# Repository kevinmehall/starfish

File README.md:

This tiny board provides a 12-pin Pmod port, controlled over USB. [Pmod](http://www.digilentinc.com/Pmods/Digilent-Pmod_%20Interface_Specification.pdf) is a standard pinout for SPI, I2C, UART, and GPIO on a 6 or 12 pin connector, with over 100 modules available from several companies. 

Level shifters and a digitally-controlled voltage regulator allow it to operate at 1.2 - 5V IO levels. 

Key components:

  * [Atmel SAMD21](http://www.atmel.com/Images/Atmel-42181-SAM-D21_Datasheet.pdf) - Cortex M0+ microcontroller
  * [Fairchild FXMAR2104](https://www.fairchildsemi.com/datasheets/FX/FXMAR2104.pdf) - IO level shifter

Firmware bringup is in progress. It will work with the [Tessel 2 JavaScript API](https://github.com/tessel/t2-firmware) and [Signalspec](http://signalspec.org).

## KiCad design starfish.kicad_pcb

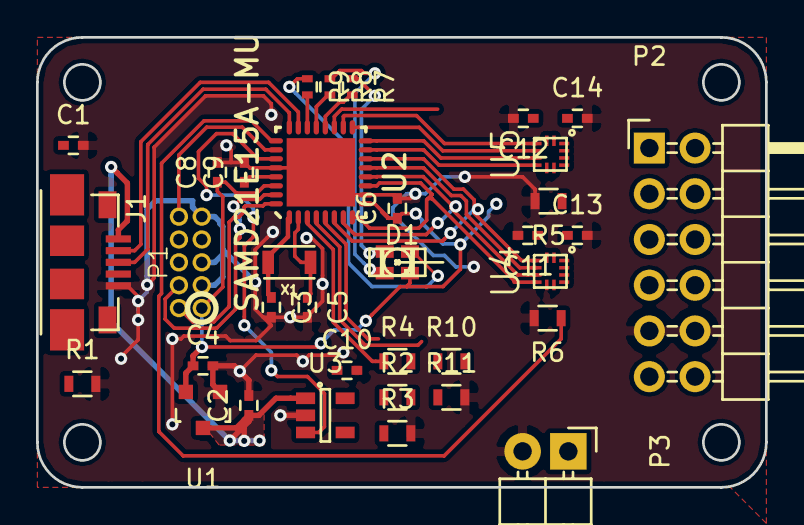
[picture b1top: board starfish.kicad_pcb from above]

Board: 2 copper layers, 40.5 x 25.0 mm, 35 parts (0 on the bottom side), 42 nets.

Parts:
C1, C3, C5: 10pF; C_0402
C2, C4, C10: 1uF; C_0402
C6, C8, C9, C11, C12, C13, C14: 100nF; C_0402
D1: LED-RGB-COMMON-ANODE; LED-1206-RGB
J1: microUSB; MICRO-USB-10104111
P1: CONN_02X05; CONN_02x05_0.05in
P2: CONN_6X2; Pin_Header_Angled_2x06
P3: CONN_2; Pin_Header_Angled_1x02
R1, R2, R3, R4, R5, R6, R10, R11: R; R_0603
R7, R8, R9: 120; R_0402
U1: AP2120N; SOT-23
U2: SAMD21E15A-MU; QFP32
U3: TPS73101; SOT-23-5
U4, U5: FXMAR2104; UMLP-12
X1: CRYSTAL; FC-135

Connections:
+3.3V: C4.1, C6.1, C8.1, C11.1, C12.1, D1.4, P1.1, U1.2, U2.9, U2.30, U4.2, U5.2
+5V: C2.1, J1.1, U1.3, U3.1
/ADC: P3.1, U2.5
/ADC_P: R10.2, R11.1, U2.4
/DAC: R4.1, U2.3
/EN_P: U2.27, U3.3
/EN_X: R6.1, U2.25, U4.8
/EN_Y: R5.1, U2.19, U5.8
/LED_B: R9.2, U2.22
/LED_G: R8.2, U2.21
/LED_R: R7.2, U2.20
/SWCLK: P1.2, U2.32
/SWDIO: P1.4, U2.31
/USB+: J1.3, U2.24
/USB-: J1.2, U2.23
/X1: P2.1, U4.10
/X1M: U2.7, U2.12, U4.5
/X2: P2.3, U4.9
/X2M: U2.8, U2.11, U4.6
/X3: P2.5, U4.11
/X3M: U2.13, U4.4
/X4: P2.7, U4.12
/X4M: U2.6, U2.14, U4.3
/Y1: P2.2, U5.11
/Y1M: U2.17, U5.4
/Y2: P2.4, U5.12
/Y2M: U2.18, U5.3
/Y3: P2.6, U5.9
/Y3M: U2.15, U5.6
/Y4: P2.8, U5.10
/Y4M: U2.16, U5.5
/~RESET: P1.10, U2.26
GND: C1.2, C2.2, C3.2, C4.2, C5.2, C6.2, C8.2, C9.2, C10.2, C11.2, C12.2, C13.2, C14.2, J1.5, P1.3, P1.5, P1.9, P2.9, P2.10, P3.2, R1.2, R3.2, R5.2, R6.2, R11.2, U1.1, U2.0, U2.10, U2.28, U3.2, U4.7, U5.7
unnamed: C1.1, J1.0, R1.1
unnamed: C3.1, U2.1, X1.1
unnamed: C5.1, U2.2, X1.2
unnamed: C9.1, U2.29
unnamed: D1.1, R9.1
unnamed: D1.2, R7.1
unnamed: D1.3, R8.1
unnamed: R2.2, R3.1, R4.2, U3.4
VAA: C10.1, C13.1, C14.1, P2.11, P2.12, R2.1, R10.1, U3.5, U4.1, U5.1

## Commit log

2015-04-14 Fully routed
2015-04-14 Add pin mux notes
2015-05-24 Add README
